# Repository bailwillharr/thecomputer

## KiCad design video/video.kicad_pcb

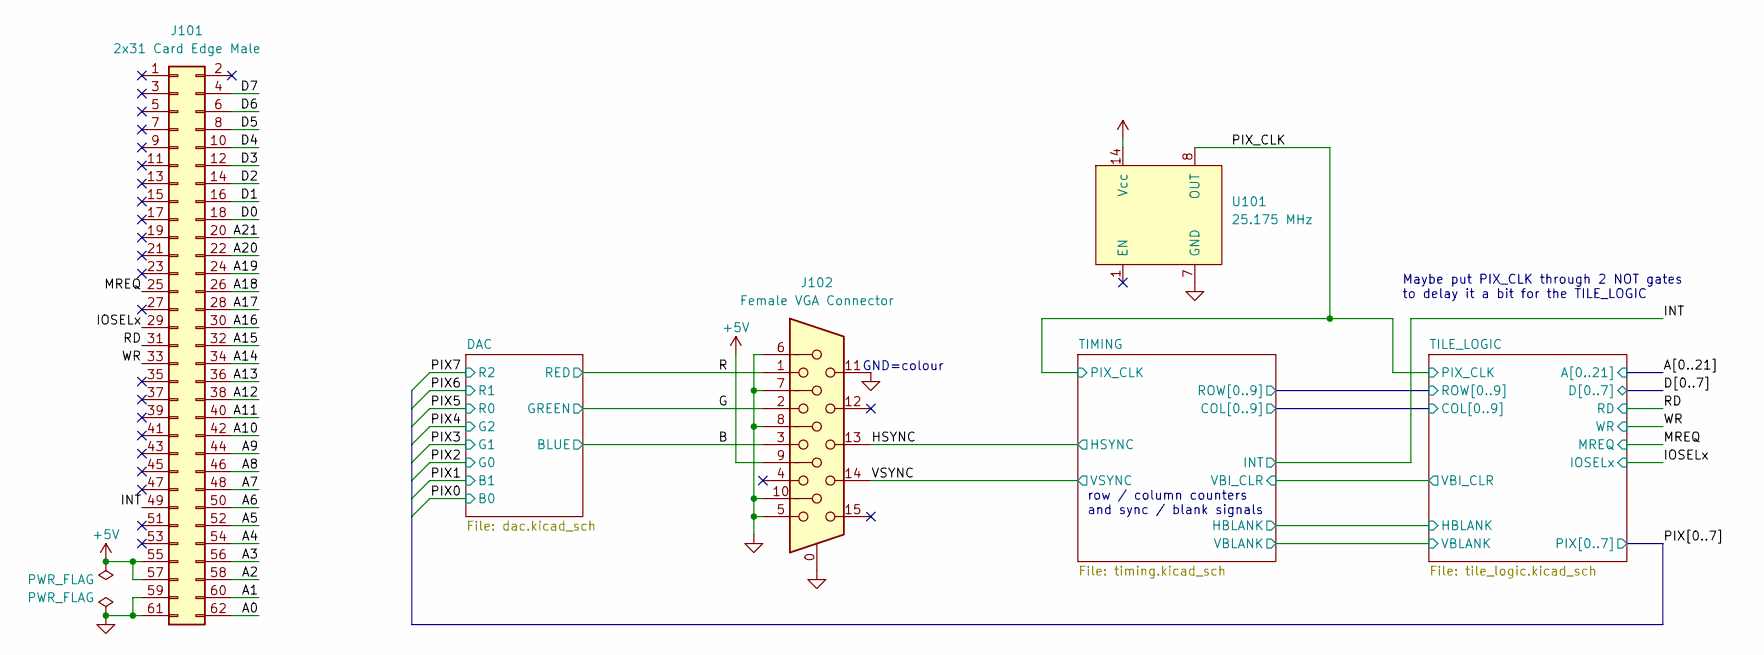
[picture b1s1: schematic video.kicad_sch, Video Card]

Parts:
J101: 2x31 Card Edge Male; PinHeader_2x31_P2.54mm_Horizontal_AltPins
J102: Female VGA Connector; DSUB-15-HD_Female_Horizontal_P2.29x1.98mm_EdgePinOffset8.35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; Digikey Part No. 609-5180-ND
U101: 25.175 MHz; Oscillator_DIP-14_LargePads; Digikey Part No. X130-ND

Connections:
+5V: J101.55, J101.57, J102.9, U101.14 (Vcc); also elsewhere on the board
/A0: J101.62; also elsewhere on the board
/A1: J101.60; also elsewhere on the board
/A2: J101.58; also elsewhere on the board
/A3: J101.56; also elsewhere on the board
/A4: J101.54; also elsewhere on the board
/A5: J101.52; also elsewhere on the board
/A6: J101.50; also elsewhere on the board
/A7: J101.48; also elsewhere on the board
/A8: J101.46; also elsewhere on the board
/A9: J101.44; also elsewhere on the board
/A10: J101.42; also elsewhere on the board
/A11: J101.40; also elsewhere on the board
/A12: J101.38; also elsewhere on the board
/A13: J101.36; also elsewhere on the board
/A14: J101.34; also elsewhere on the board
/A15: J101.32; also elsewhere on the board
/A16: J101.30; also elsewhere on the board
/A17: J101.28; also elsewhere on the board
/A18: J101.26; also elsewhere on the board
/A19: J101.24; also elsewhere on the board
/A20: J101.22; also elsewhere on the board
/A21: J101.20; also elsewhere on the board
/B: J102.3; also elsewhere on the board
/D0: J101.18; also elsewhere on the board
/D1: J101.16; also elsewhere on the board
/D2: J101.14; also elsewhere on the board
/D3: J101.12; also elsewhere on the board
/D4: J101.10; also elsewhere on the board
/D5: J101.8; also elsewhere on the board
/D6: J101.6; also elsewhere on the board
/D7: J101.4; also elsewhere on the board
/G: J102.2; also elsewhere on the board
/HSYNC: J102.13; also elsewhere on the board
/INT: J101.49; also elsewhere on the board
/IOSELx: J101.29; also elsewhere on the board
/MREQ: J101.25; also elsewhere on the board
/PIX_CLK: U101.8 (OUT); also elsewhere on the board
/R: J102.1; also elsewhere on the board
/RD: J101.31; also elsewhere on the board
/VSYNC: J102.14; also elsewhere on the board
/WR: J101.33; also elsewhere on the board
GND: J101.59, J101.61, J102.0, J102.5, J102.6, J102.7, J102.8, J102.10, J102.11, U101.7 (GND); also elsewhere on the board

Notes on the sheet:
GND=colour
Maybe put PIX_CLK through 2 NOT gates to delay it a bit for the TILE_LOGIC
row / column counters and sync / blank signals

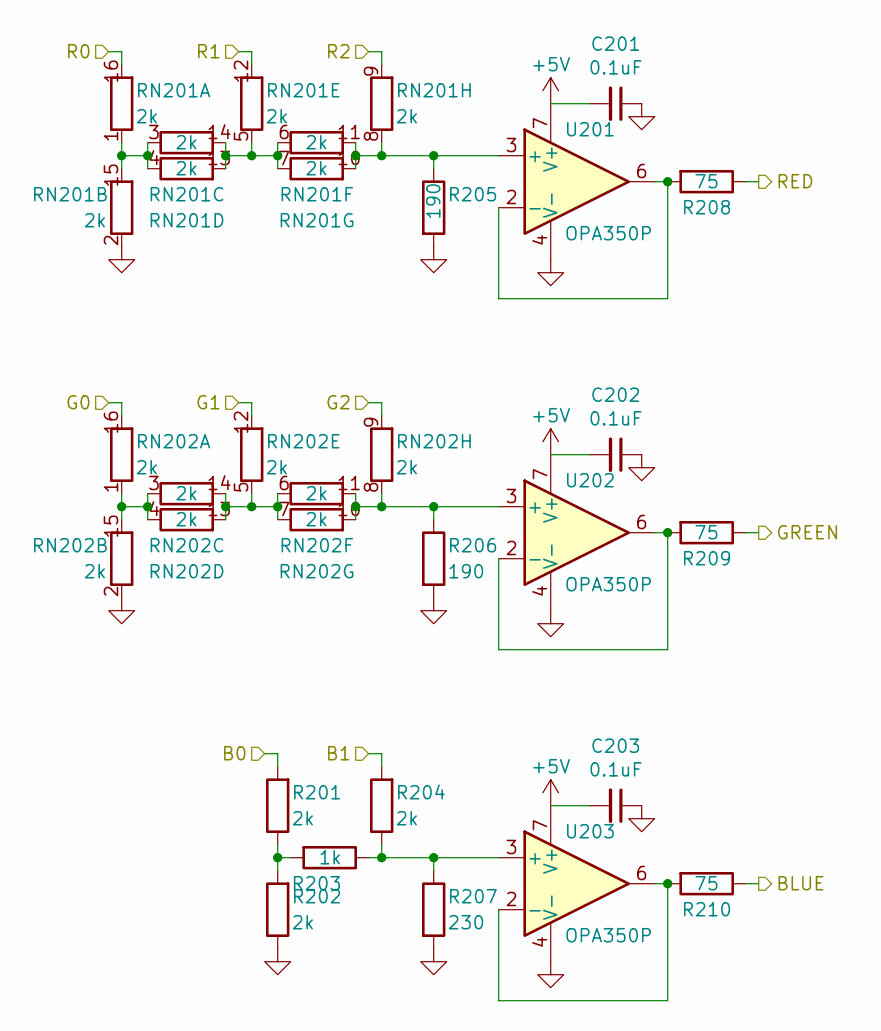
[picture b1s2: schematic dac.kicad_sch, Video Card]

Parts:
C201, C202, C203: 0.1uF; C_Disc_D5.0mm_W2.5mm_P2.50mm; Digikey Part No. 399-9859-1-ND
R201, R202, R204: 2k; R_Axial_DIN0207_L6.3mm_D2.5mm_P10.16mm_Horizontal; Digikey Part No. RNF14FTD2K00
R203: 1k; R_Axial_DIN0207_L6.3mm_D2.5mm_P10.16mm_Horizontal
R205, R206: 190; R_Axial_DIN0207_L6.3mm_D2.5mm_P10.16mm_Horizontal; Digikey Part No. 191XBK-ND
R207: 230; R_Axial_DIN0207_L6.3mm_D2.5mm_P10.16mm_Horizontal; Digikey Part No. 232XBK-ND
R208, R209, R210: 75; R_Axial_DIN0207_L6.3mm_D2.5mm_P10.16mm_Horizontal; Digikey Part No. RNF14FTD75R0CT-ND
RN201, RN202: 2k; DIP-16_W7.62mm_Socket; Digikey Part No. 4116R-1-202LF-ND
U201, U202, U203: OPA350P; DIP-8_W7.62mm; Digikey Part No. OPA350PA-ND

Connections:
+5V: C201.2, C202.2, C203.2, U201.7 (V+), U202.7 (V+), U203.7 (V+); also elsewhere on the board
/B: R210.1; also elsewhere on the board
/G: R209.1; also elsewhere on the board
/PIX0: R201.2; also elsewhere on the board
/PIX1: R204.2; also elsewhere on the board
/PIX2: RN202.16 (R1.2); also elsewhere on the board
/PIX3: RN202.12 (R5.2); also elsewhere on the board
/PIX4: RN202.9 (R8.2); also elsewhere on the board
/PIX5: RN201.16 (R1.2); also elsewhere on the board
/PIX6: RN201.12 (R5.2); also elsewhere on the board
/PIX7: RN201.9 (R8.2); also elsewhere on the board
/R: R208.1; also elsewhere on the board
GND: C201.1, C202.1, C203.1, R202.1, R205.2, R206.2, R207.2, RN201.2 (R2.1), RN202.2 (R2.1), U201.4 (V-), U202.4 (V-), U203.4 (V-); also elsewhere on the board
unnamed: R201.1, R202.2, R203.2
unnamed: RN201.1 (R1.1), RN201.3 (R3.1), RN201.4 (R4.1), RN201.15 (R2.2)
unnamed: RN201.5 (R5.1), RN201.6 (R6.1), RN201.7 (R7.1), RN201.13 (R4.2), RN201.14 (R3.2)
unnamed: R205.1, RN201.8 (R8.1), RN201.10 (R7.2), RN201.11 (R6.2), U201.3 (+)
unnamed: RN202.1 (R1.1), RN202.3 (R3.1), RN202.4 (R4.1), RN202.15 (R2.2)
unnamed: RN202.5 (R5.1), RN202.6 (R6.1), RN202.7 (R7.1), RN202.13 (R4.2), RN202.14 (R3.2)
unnamed: R206.1, RN202.8 (R8.1), RN202.10 (R7.2), RN202.11 (R6.2), U202.3 (+)
unnamed: R208.2, U201.2 (-), U201.6
unnamed: R209.2, U202.2 (-), U202.6
unnamed: R203.1, R204.1, R207.1, U203.3 (+)
unnamed: R210.2, U203.2 (-), U203.6

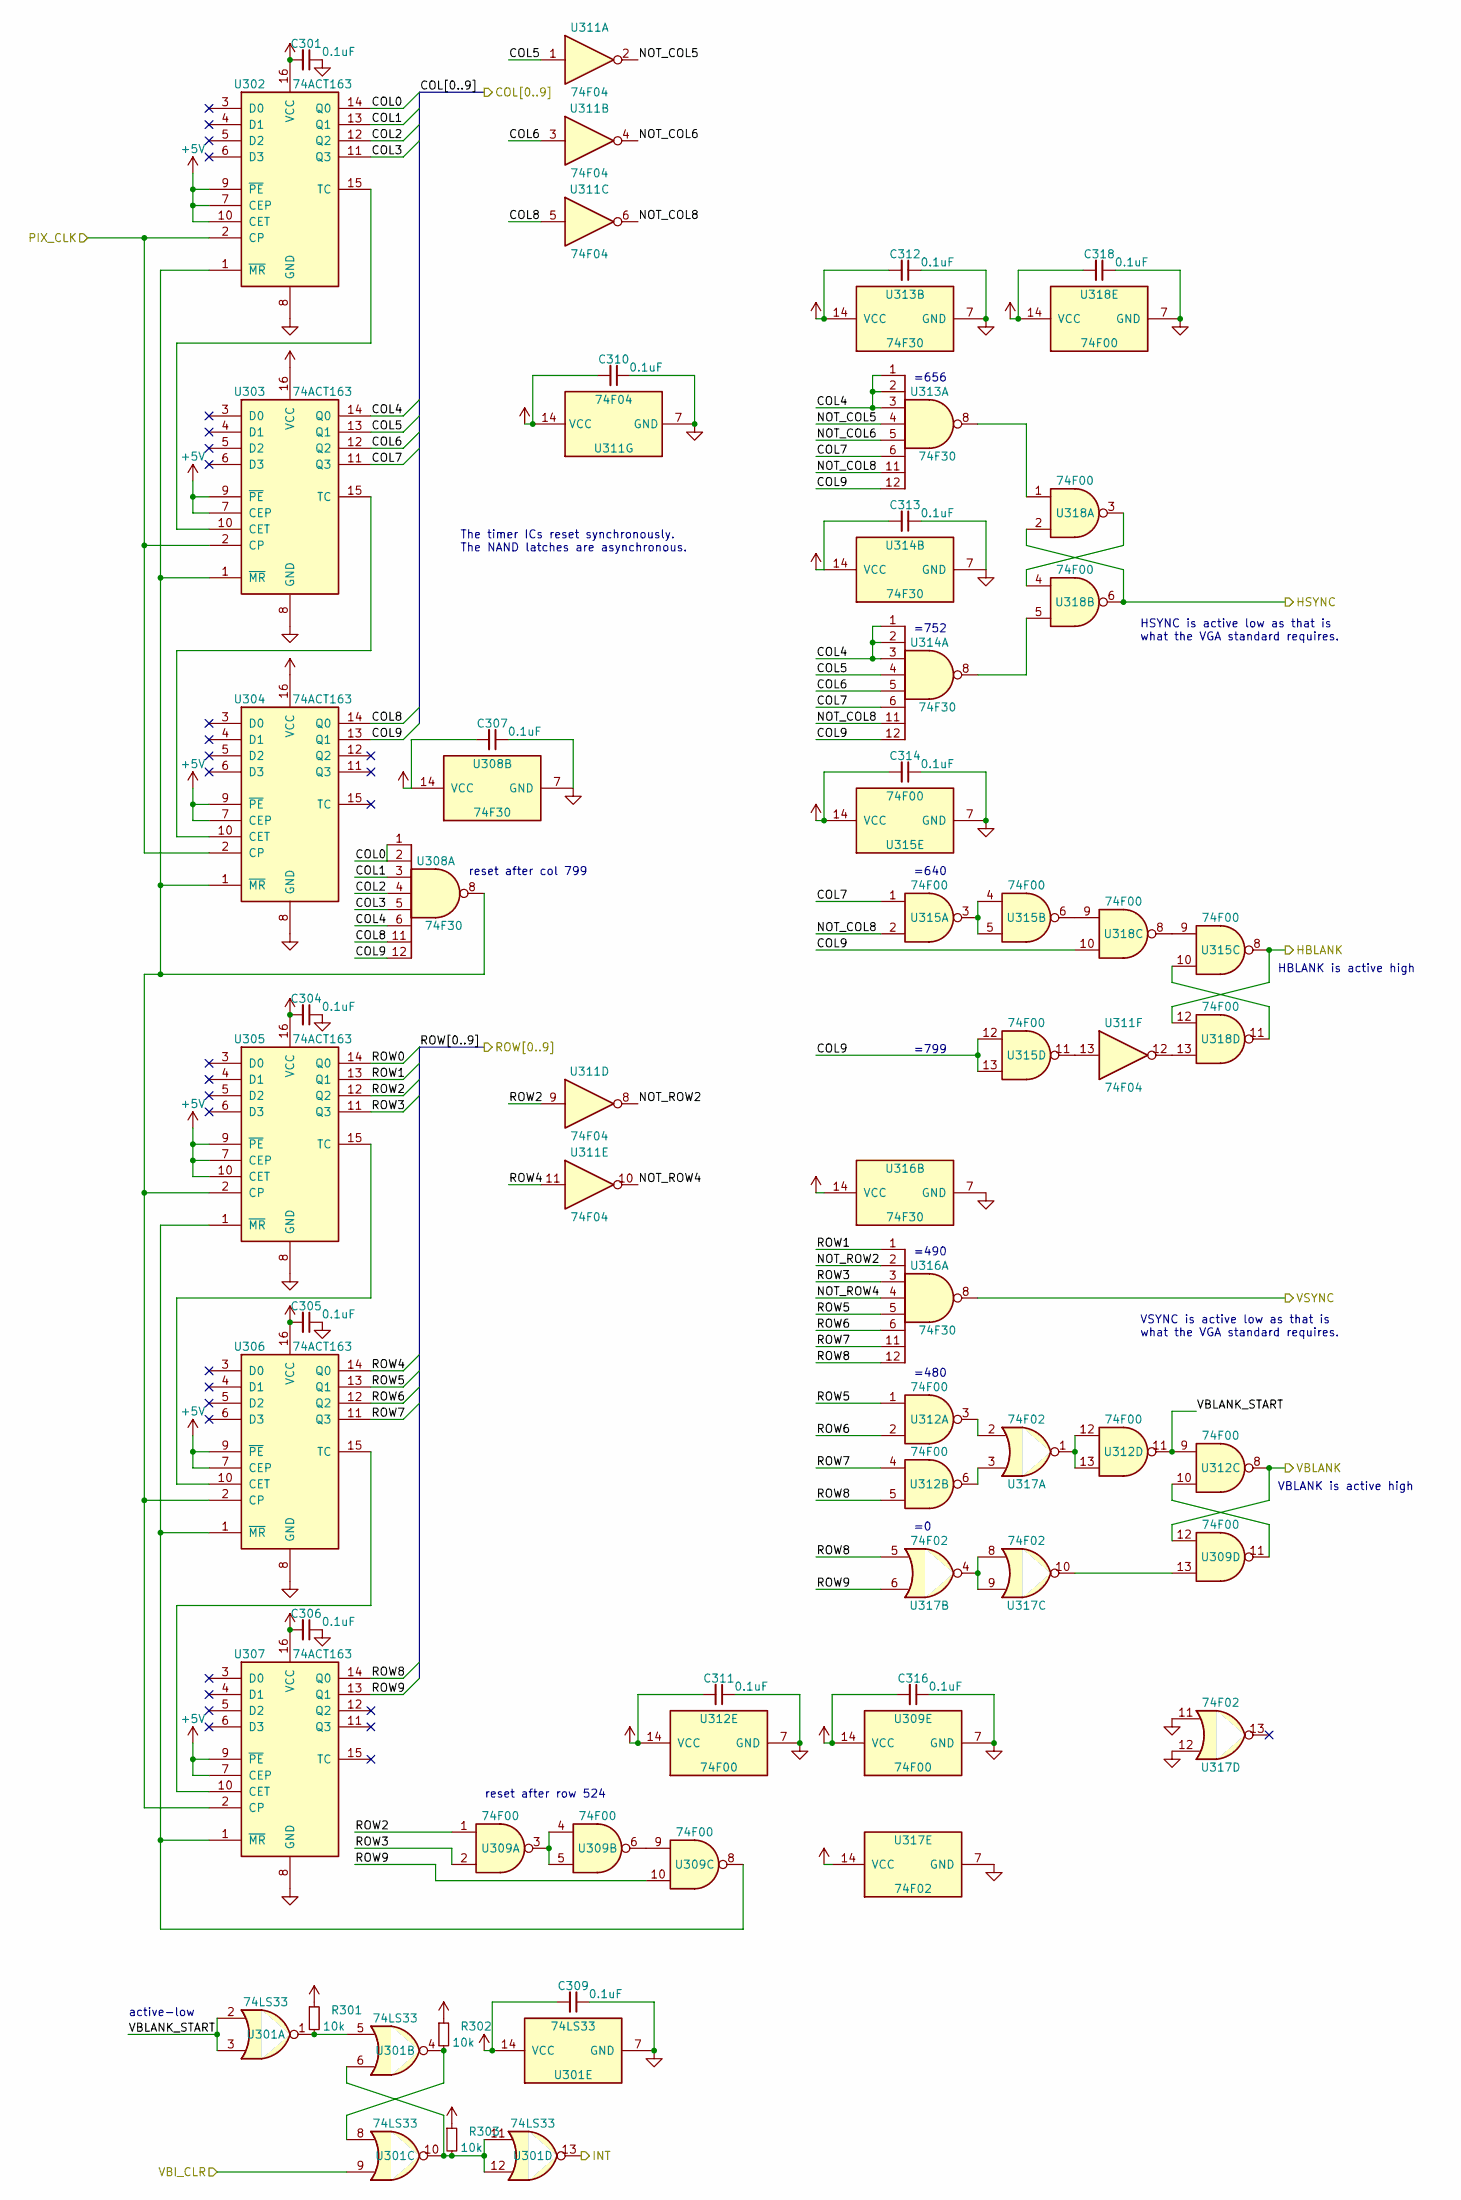
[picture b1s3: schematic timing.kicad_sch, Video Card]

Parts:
C301, C304, C305, C306, C307, C309, C310, C311, C312, C313, C314, C316, C318: 0.1uF; C_Disc_D5.0mm_W2.5mm_P2.50mm; Digikey Part No. 399-9859-1-ND
R301, R302, R303: 10k; R_Axial_DIN0207_L6.3mm_D2.5mm_P10.16mm_Horizontal; Digikey Part No. CF14JT10K0CT-ND
U301: 74LS33; DIP-14_W7.62mm_Socket; Digikey Part No. 296-3699-5-ND
U302, U303, U304, U305, U306, U307: 74ACT163; DIP-16_W7.62mm_Socket; Digikey Part No. 296-32983-5-ND
U308, U313, U314, U316: 74F30; DIP-14_W7.62mm_Socket; Digikey Part No. 296-SN74F30N-ND
U309, U312, U315, U318: 74F00; DIP-14_W7.62mm_Socket; Digikey Part No. 296-3539-5-ND
U311: 74F04; DIP-14_W7.62mm_Socket; Digikey Part No. 296-3542-5-ND
U317: 74F02; DIP-14_W7.62mm_Socket; Digikey Part No. 296-3541-5-ND

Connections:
+5V: C301.2, C304.2, C305.2, C306.2, C307.2, C309.2, C310.2, C311.2, C312.2, C313.2, C314.2, C316.2, C318.2, R301.1, R302.1, R303.1, U301.14 (VCC), U302.7 (CEP), U302.9 (~PE), U302.10 (CET), U302.16 (VCC), U303.7 (CEP), U303.9 (~PE), U303.16 (VCC), U304.7 (CEP), U304.9 (~PE), U304.16 (VCC), U305.7 (CEP), U305.9 (~PE), U305.10 (CET), U305.16 (VCC), U306.7 (CEP), U306.9 (~PE), U306.16 (VCC), U307.7 (CEP), U307.9 (~PE), U307.16 (VCC), U308.14 (VCC), U309.14 (VCC), U311.14 (VCC), U312.14 (VCC), U313.14 (VCC), U314.14 (VCC), U315.14 (VCC), U316.14 (VCC), U317.14 (VCC), U318.14 (VCC); also elsewhere on the board
/HSYNC: U318.2, U318.6; also elsewhere on the board
/INT: U301.13; also elsewhere on the board
/PIX_CLK: U302.2 (CP), U303.2 (CP), U304.2 (CP); also elsewhere on the board
/TILE_LOGIC/HBLANK: U315.8, U318.12; also elsewhere on the board
/TILE_LOGIC/VBI_CLR: U301.9; also elsewhere on the board
/TILE_LOGIC/VBLANK: U309.12, U312.8; also elsewhere on the board
/TIMING/COL0: U302.14 (Q0), U308.1, U308.2; also elsewhere on the board
/TIMING/COL1: U302.13 (Q1), U308.3; also elsewhere on the board
/TIMING/COL2: U302.12 (Q2), U308.4; also elsewhere on the board
/TIMING/COL3: U302.11 (Q3), U308.5; also elsewhere on the board
/TIMING/COL4: U303.14 (Q0), U308.6, U313.1, U313.2, U313.3, U314.1, U314.2, U314.3; also elsewhere on the board
/TIMING/COL5: U303.13 (Q1), U311.1, U314.4; also elsewhere on the board
/TIMING/COL6: U303.12 (Q2), U311.3, U314.5; also elsewhere on the board
/TIMING/COL7: U303.11 (Q3), U313.6, U314.6, U315.1; also elsewhere on the board
/TIMING/COL8: U304.14 (Q0), U308.11, U311.5; also elsewhere on the board
/TIMING/COL9: U304.13 (Q1), U308.12, U313.12, U314.12, U315.12, U315.13, U318.10; also elsewhere on the board
/TIMING/NOT_COL5: U311.2, U313.4
/TIMING/NOT_COL6: U311.4, U313.5
/TIMING/NOT_COL8: U311.6, U313.11, U314.11, U315.2
/TIMING/NOT_ROW2: U311.8, U316.2
/TIMING/NOT_ROW4: U311.10, U316.4
/TIMING/ROW0: U305.14 (Q0); also elsewhere on the board
/TIMING/ROW1: U305.13 (Q1), U316.1; also elsewhere on the board
/TIMING/ROW2: U305.12 (Q2), U309.1, U311.9; also elsewhere on the board
/TIMING/ROW3: U305.11 (Q3), U309.2, U316.3; also elsewhere on the board
/TIMING/ROW4: U306.14 (Q0), U311.11; also elsewhere on the board
/TIMING/ROW5: U306.13 (Q1), U312.1, U316.5; also elsewhere on the board
/TIMING/ROW6: U306.12 (Q2), U312.2, U316.6; also elsewhere on the board
/TIMING/ROW7: U306.11 (Q3), U312.4, U316.11; also elsewhere on the board
/TIMING/ROW8: U307.14 (Q0), U312.5, U316.12, U317.5; also elsewhere on the board
/TIMING/ROW9: U307.13 (Q1), U309.10, U317.6; also elsewhere on the board
/TIMING/VBLANK_START: U301.2, U301.3, U312.9, U312.11
/VSYNC: U316.8; also elsewhere on the board
GND: C301.1, C304.1, C305.1, C306.1, C307.1, C309.1, C310.1, C311.1, C312.1, C313.1, C314.1, C316.1, C318.1, U301.7 (GND), U302.8 (GND), U303.8 (GND), U304.8 (GND), U305.8 (GND), U306.8 (GND), U307.8 (GND), U308.7 (GND), U309.7 (GND), U311.7 (GND), U312.7 (GND), U313.7 (GND), U314.7 (GND), U315.7 (GND), U316.7 (GND), U317.7 (GND), U317.11, U317.12, U318.7 (GND); also elsewhere on the board
unnamed: R301.2, U301.1, U301.5
unnamed: R302.2, U301.4, U301.8
unnamed: R303.2, U301.6, U301.10, U301.11, U301.12
unnamed: U302.15 (TC), U303.10 (CET)
unnamed: U302.1 (~MR), U303.1 (~MR), U304.1 (~MR), U305.2 (CP), U306.2 (CP), U307.2 (CP), U308.8
unnamed: U303.15 (TC), U304.10 (CET)
unnamed: U305.15 (TC), U306.10 (CET)
unnamed: U305.1 (~MR), U306.1 (~MR), U307.1 (~MR), U309.8
unnamed: U306.15 (TC), U307.10 (CET)
unnamed: U309.3, U309.4, U309.5
unnamed: U309.6, U309.9
unnamed: U309.11, U312.10
unnamed: U309.13, U317.10
unnamed: U311.12, U318.13
unnamed: U311.13, U315.11
unnamed: U312.3, U317.2
unnamed: U312.6, U317.3
unnamed: U312.12, U312.13, U317.1
unnamed: U313.8, U318.1
unnamed: U314.8, U318.5
unnamed: U315.3, U315.4, U315.5
unnamed: U315.6, U318.9
unnamed: U315.9, U318.8
unnamed: U315.10, U318.11
unnamed: U317.4, U317.8, U317.9
unnamed: U318.3, U318.4

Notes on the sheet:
active-low
HBLANK is active high
reset after col 799
=656
=480
VSYNC is active low as that is what the VGA standard requires.
=752
=799
HSYNC is active low as that is what the VGA standard requires.
The timer ICs reset synchronously. The NAND latches are asynchronous.
reset after row 524
VBLANK is active high
=640
=490
